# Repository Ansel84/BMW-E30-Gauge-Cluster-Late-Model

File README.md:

# BMW E30 Gauge Cluster Late Model
The goal for this project is to reverse engineer every PCB in the gauge cluster for Late model year BMW E30's. This includes the main PCB referred to as the "Nexus" board, the SI (Service Interval) board, and the smaller boards that are part of the tachometer and speedometer gauge assemblies.

# Early Model Clusters:
If you have an early model cluster and need parts for that, check out the progress of the early model project here: https://github.com/Ansel84/BMW-E30-Gauge-Cluster-Early-Model

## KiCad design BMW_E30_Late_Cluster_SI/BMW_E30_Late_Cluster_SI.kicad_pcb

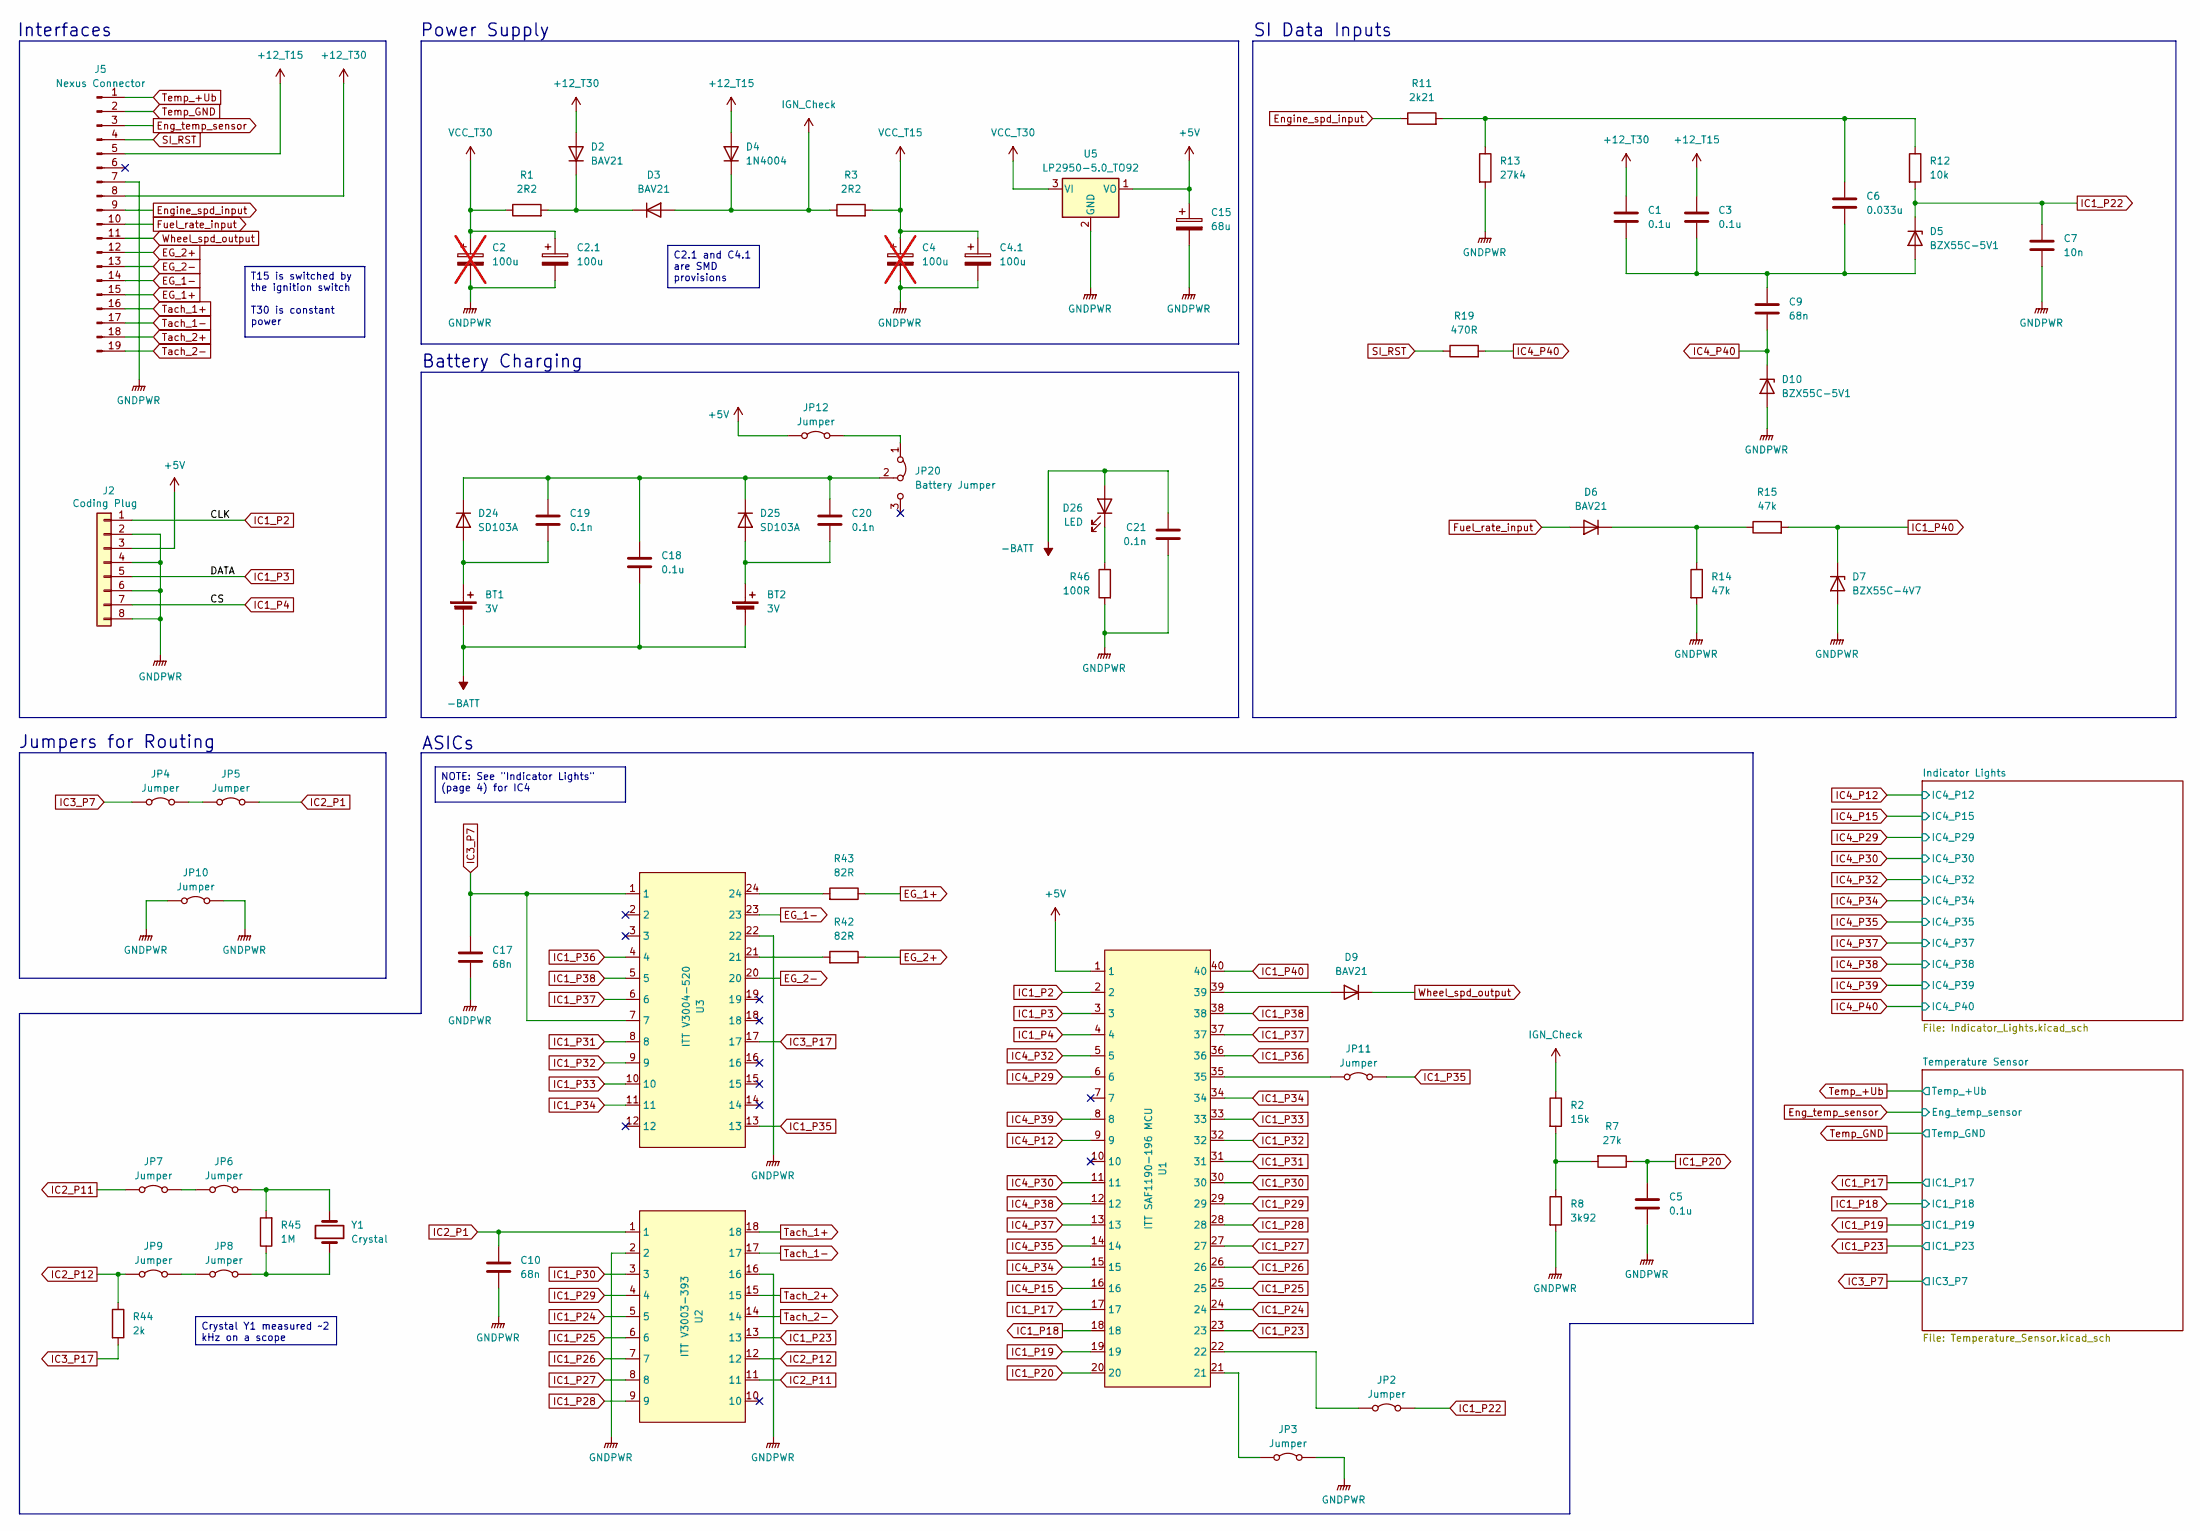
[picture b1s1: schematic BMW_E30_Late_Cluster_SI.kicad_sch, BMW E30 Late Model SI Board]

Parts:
BT1, BT2: 3V; Batt_CR14250SE
C1, C3: 0.1u; C_Disc_D6.0mm_W2.5mm_P5.00mm
C2, C4: 100u; CP_Axial_L18.0mm_D6.5mm_P25.00mm_Horizontal; not fitted
C2.1, C4.1: 100u; CP_Elec_6.3x5.8
C5, C18: 0.1u; C_Rect_L7.0mm_W2.0mm_P5.00mm
C6: 0.033u; C_Rect_L7.0mm_W2.0mm_P5.00mm
C7: 10n; C_Rect_L7.0mm_W2.0mm_P5.00mm
C9, C10, C17: 68n; C_Disc_D6.0mm_W2.5mm_P5.00mm
C15: 68u; CP_Radial_Tantal_D5.5mm_P5.00mm
C19, C20, C21: 0.1n; C_Disc_D6.0mm_W2.5mm_P5.00mm
D2, D3, D6, D9: BAV21; D_Axial_Narrow_L6.7mm_D2.4mm_P9.7mm
D4: 1N4004; D_Axial_Narrow_L6.7mm_D2.4mm_P9.7mm
D5, D10: BZX55C-5V1; D_Axial_Narrow_L6.7mm_D2.4mm_P9.7mm
D7: BZX55C-4V7; D_Axial_Narrow_L6.7mm_D2.4mm_P9.7mm
D24, D25: SD103A; D_Axial_Narrow_L6.7mm_D2.4mm_P9.7mm
D26: LED; LED_D3.0mm
J2: Coding Plug; PinSocket_1x08_P2.54mm_Horizontal
J5: Nexus Connector; E30_Early_SI_Conn_Late_P3.5
JP2, JP3, JP4, JP5, JP6, JP7, JP8, JP9, JP10, JP11, JP12: Jumper; Jumper_THT_P9.7mm
JP20: Battery Jumper; PinHeader_1x03_P2.54mm_Vertical
R1, R3: 2R2; R_Axial_Narrow_L6.8mm_D2.4mm_P9.7mm
R2: 15k; R_Axial_Narrow_L6.8mm_D2.4mm_P9.7mm
R7: 27k; R_Axial_Narrow_L6.8mm_D2.4mm_P9.7mm
R8: 3k92; R_Axial_Narrow_L6.8mm_D2.4mm_P9.7mm
R11: 2k21; R_Axial_Narrow_L6.8mm_D2.4mm_P9.7mm
R12: 10k; R_Axial_Narrow_L6.8mm_D2.4mm_P9.7mm
R13: 27k4; R_Axial_Narrow_L6.8mm_D2.4mm_P9.7mm
R14, R15: 47k; R_Axial_Narrow_L6.8mm_D2.4mm_P9.7mm
R19: 470R; R_Axial_Narrow_L6.8mm_D2.4mm_P9.7mm
R42, R43: 82R; R_Axial_Narrow_L6.8mm_D2.4mm_P9.7mm
R44: 2k; R_Axial_Narrow_L6.8mm_D2.4mm_P22.4mm
R45: 1M; R_Axial_Narrow_L6.8mm_D2.4mm_P9.7mm
R46: 100R; R_Axial_Narrow_L6.8mm_D2.4mm_P9.7mm
U1: ITT SAF1190-196 MCU; DIP-40_W15.24mm_LongPads
U2: ITT V3003-393; DIP-18_W7.62mm_LongPads
U3: ITT V3004-520; DIP-24_W15.24mm_LongPads
U5: LP2950-5.0_TO92; TO-92_Inline_Wide
Y1: Crystal; Crystal_HC18-U_Vertical

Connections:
+5V: C15.1, J2.3, JP12.1 (A), U1.1, U5.1 (VO); also elsewhere on the board
+12_T15: C3.1, D4.2 (A), J5.5
+12_T30: C1.1, D2.2 (A), J5.8; also elsewhere on the board
-BATT: BT1.2 (-), BT2.2 (-), C18.2, C21.1, D26.2 (A); also elsewhere on the board
EG_1+: J5.15, R43.1
EG_1-: J5.14, U3.23
EG_2+: J5.12, R42.1
EG_2-: J5.13, U3.20
Eng_temp_sensor: J5.3; also elsewhere on the board
Engine_spd_input: J5.9, R11.1
Fuel_rate_input: D6.2 (A), J5.10
GNDPWR: C2.2, C2.1.2, C4.2, C4.1.2, C5.2, C7.2, C10.2, C15.2, C17.2, C21.2, D7.2 (A), D10.2 (A), J2.2, J2.4, J2.6, J2.8, J5.7, JP3.1 (A), JP10.1 (A), JP10.2 (B), R8.2, R13.2, R14.2, R46.2, U2.2, U2.16, U3.22, U5.2 (GND); also elsewhere on the board
IC1_P2: J2.1, U1.2
IC1_P3: J2.5, U1.3
IC1_P4: J2.7, U1.4
IC1_P17: U1.17; also elsewhere on the board
IC1_P18: U1.18; also elsewhere on the board
IC1_P19: U1.19; also elsewhere on the board
IC1_P20: C5.1, R7.1, U1.20
IC1_P22: C7.1, D5.1 (K), JP2.1 (A), R12.2
IC1_P23: U1.23, U2.13; also elsewhere on the board
IC1_P24: U1.24, U2.5
IC1_P25: U1.25, U2.6
IC1_P26: U1.26, U2.7
IC1_P27: U1.27, U2.8
IC1_P28: U1.28, U2.9
IC1_P29: U1.29, U2.4
IC1_P30: U1.30, U2.3
IC1_P31: U1.31, U3.8
IC1_P32: U1.32, U3.9
IC1_P33: U1.33, U3.10
IC1_P34: U1.34, U3.11
IC1_P35: JP11.1 (A), U3.13
IC1_P36: U1.36, U3.4
IC1_P37: U1.37, U3.6
IC1_P38: U1.38, U3.5
IC1_P40: D7.1 (K), R15.2, U1.40
IC2_P1: C10.1, JP5.2 (B), U2.1
IC2_P11: JP7.2 (B), U2.11
IC2_P12: JP9.1 (A), R44.1, U2.12
IC3_P7: C17.1, JP4.1 (A), U3.1, U3.7; also elsewhere on the board
IC3_P17: R44.2, U3.17
IC4_P12: U1.9; also elsewhere on the board
IC4_P15: U1.16; also elsewhere on the board
IC4_P29: U1.6; also elsewhere on the board
IC4_P30: U1.11; also elsewhere on the board
IC4_P32: U1.5; also elsewhere on the board
IC4_P34: U1.15; also elsewhere on the board
IC4_P35: U1.14; also elsewhere on the board
IC4_P37: U1.13; also elsewhere on the board
IC4_P38: U1.12; also elsewhere on the board
IC4_P39: U1.8; also elsewhere on the board
IC4_P40: C9.2, D10.1 (K), R19.2; also elsewhere on the board
IGN_Check: D3.2 (A), D4.1 (K), R2.1, R3.1
unnamed: BT1.1 (+), C19.2, D24.2 (A)
unnamed: BT2.1 (+), C20.2, D25.2 (A)
unnamed: C6.1, R11.2, R12.1, R13.1
unnamed: D2.1 (K), D3.1 (K), R1.2
unnamed: C1.2, C3.2, C6.2, C9.1, D5.2 (A)
unnamed: D6.1 (K), R14.1, R15.1
unnamed: D9.2 (A), U1.39
unnamed: C18.1, C19.1, C20.1, D24.1 (K), D25.1 (K), JP20.2 (C)
unnamed: D26.1 (K), R46.1
unnamed: JP2.2 (B), U1.22
unnamed: JP3.2 (B), U1.21
unnamed: JP4.2 (B), JP5.1 (A)
unnamed: JP6.1 (A), JP7.1 (A)
unnamed: JP6.2 (B), R45.2, Y1.2
unnamed: JP8.1 (A), JP9.2 (B)
unnamed: JP8.2 (B), R45.1, Y1.1
unnamed: JP11.2 (B), U1.35
unnamed: JP12.2 (B), JP20.1 (A)
unnamed: R2.2, R7.2, R8.1
unnamed: R42.2, U3.21
unnamed: R43.2, U3.24
SI_RST: J5.4, R19.1
Tach_1+: J5.16, U2.18
Tach_1-: J5.17, U2.17
Tach_2+: J5.18, U2.15
Tach_2-: J5.19, U2.14
Temp_+Ub: J5.1; also elsewhere on the board
Temp_GND: J5.2; also elsewhere on the board
VCC_T15: C4.1, C4.1.1, R3.2; also elsewhere on the board
VCC_T30: C2.1, C2.1.1, R1.1, U5.3 (VI)
Wheel_spd_output: D9.1 (K), J5.11

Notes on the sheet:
Power Supply
Jumpers for Routing
Battery Charging
Interfaces
ASICs
SI Data Inputs
C2.1 and C4.1 are SMD provisions
T15 is switched by the ignition switch T30 is constant power
NOTE: See "Indicator Lights" (page 4) for IC4
Crystal Y1 measured ~2 kHz on a scope

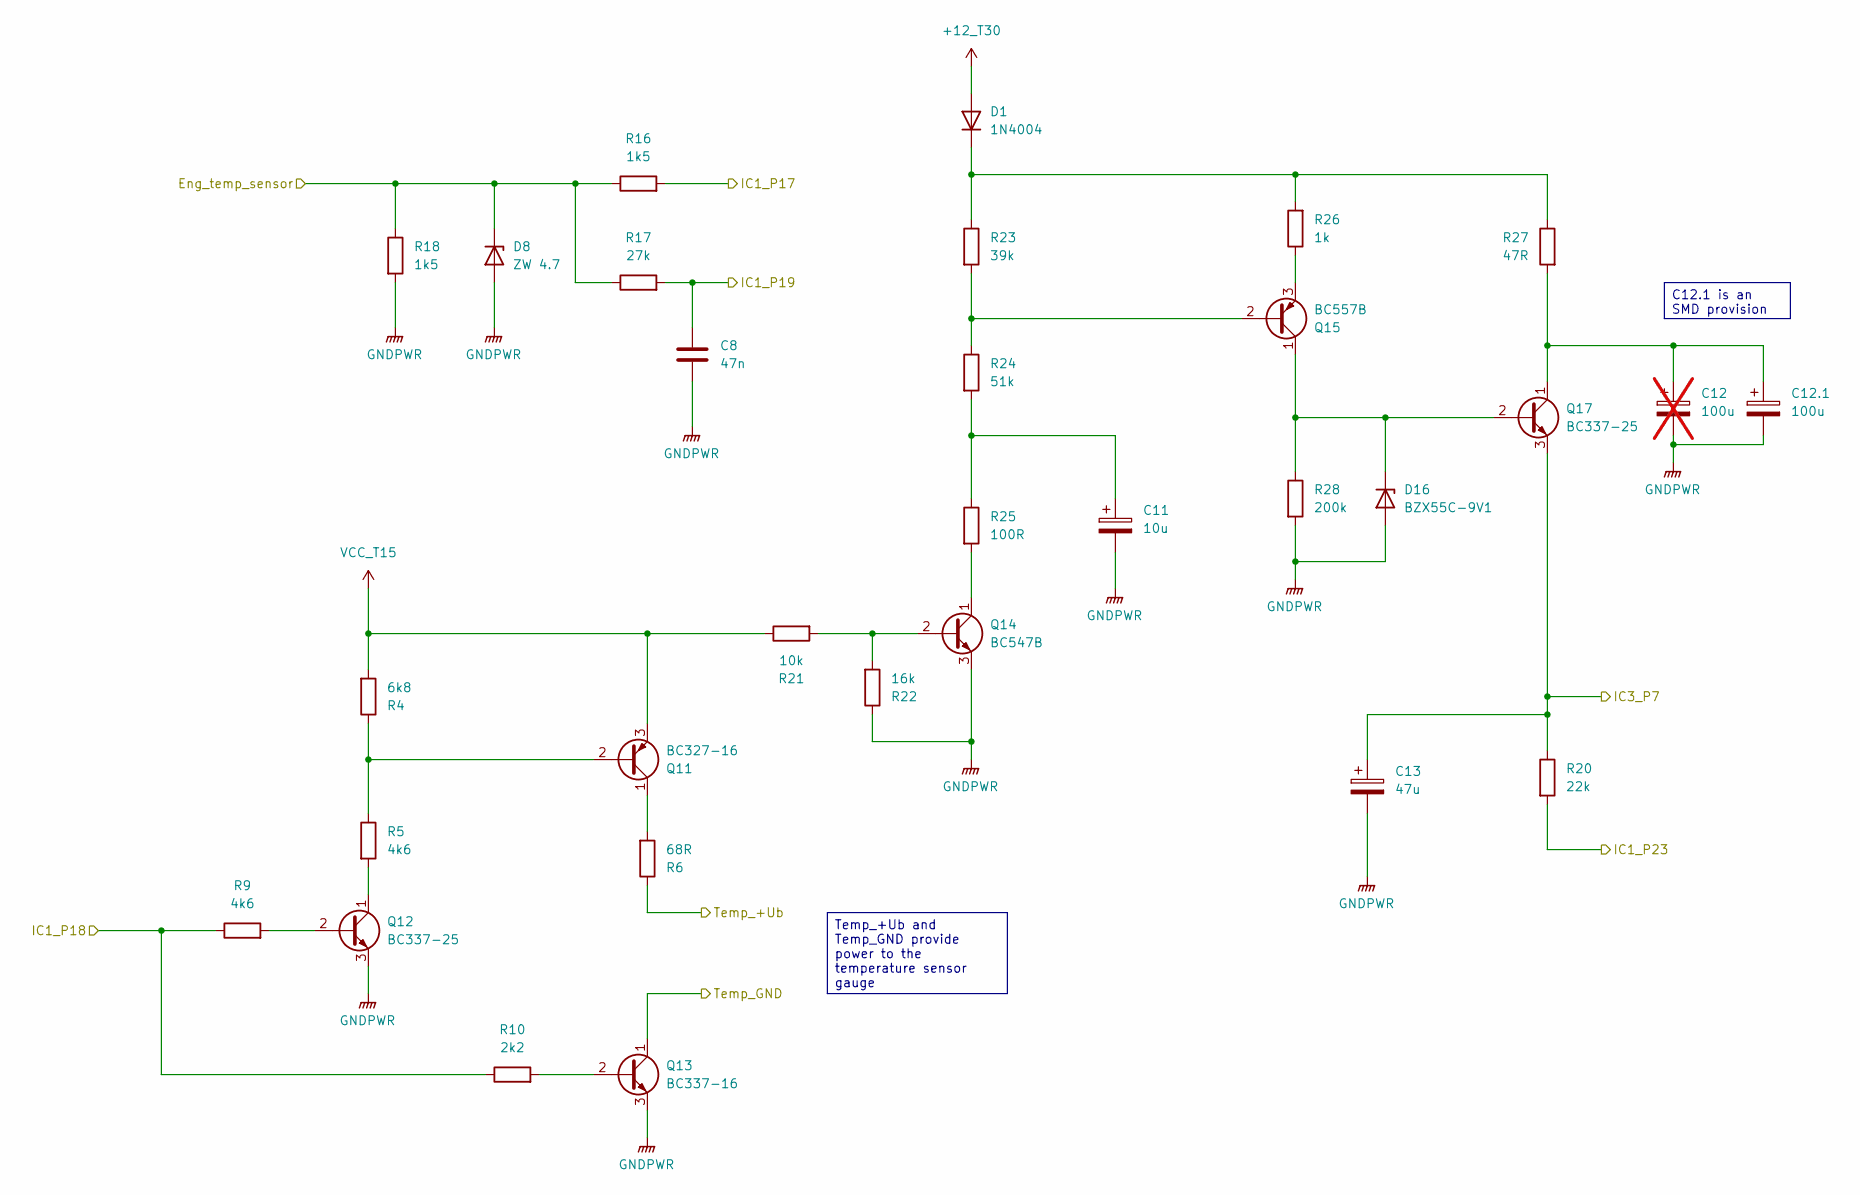
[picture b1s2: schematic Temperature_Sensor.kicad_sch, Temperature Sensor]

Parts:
C8: 47n; C_Disc_D6.0mm_W2.5mm_P5.00mm
C11: 10u; CP_Radial_Tantal_D8.0mm_P2.50mm
C12: 100u; CP_Axial_L18.0mm_D6.5mm_P25.00mm_Horizontal; not fitted
C12.1: 100u; CP_Elec_6.3x5.8
C13: 47u; CP_Radial_Tantal_D9.0mm_P2.50mm
D1: 1N4004; D_Axial_Narrow_L6.7mm_D2.4mm_P9.7mm
D8: ZW 4.7; D_Axial_Narrow_L6.7mm_D2.4mm_P9.7mm
D16: BZX55C-9V1; D_Axial_Narrow_L6.7mm_D2.4mm_P9.7mm
Q11: BC327-16; TO-92_Inline_Wide
Q12, Q17: BC337-25; TO-92_Inline_Wide
Q13: BC337-16; TO-92_Inline_Wide
Q14: BC547B; TO-92_Inline_Wide
Q15: BC557B; TO-92_Inline_Wide
R4: 6k8; R_Axial_Narrow_L6.8mm_D2.4mm_P9.7mm
R5, R9: 4k6; R_Axial_Narrow_L6.8mm_D2.4mm_P9.7mm
R6: 68R; R_Axial_DIN0414_L11.9mm_D4.5mm_P20.32mm_Horizontal
R10: 2k2; R_Axial_Narrow_L6.8mm_D2.4mm_P9.7mm
R16, R18: 1k5; R_Axial_Narrow_L6.8mm_D2.4mm_P9.7mm
R17: 27k; R_Axial_Narrow_L6.8mm_D2.4mm_P9.7mm
R20: 22k; R_Axial_DIN0207_L6.3mm_D2.5mm_P22.2mm_Horizontal
R21: 10k; R_Axial_Narrow_L6.8mm_D2.4mm_P9.7mm
R22: 16k; R_Axial_Narrow_L6.8mm_D2.4mm_P9.7mm
R23: 39k; R_Axial_Narrow_L6.8mm_D2.4mm_P9.7mm
R24: 51k; R_Axial_Narrow_L6.8mm_D2.4mm_P9.7mm
R25: 100R; R_Axial_Narrow_L6.8mm_D2.4mm_P9.7mm
R26: 1k; R_Axial_Narrow_L6.8mm_D2.4mm_P9.7mm
R27: 47R; R_Axial_DIN0516_L15.5mm_D5.0mm_P20.32mm_Horizontal
R28: 200k; R_Axial_Narrow_L6.8mm_D2.4mm_P9.7mm

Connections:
+12_T30: D1.2 (A); also elsewhere on the board
Eng_temp_sensor: D8.1 (K), R16.1, R17.1, R18.1; also elsewhere on the board
GNDPWR: C8.2, C11.2, C12.2, C12.1.2, C13.2, D8.2 (A), D16.2 (A), Q12.3 (E), Q13.3 (E), Q14.3 (E), R18.2, R22.1, R28.2; also elsewhere on the board
IC1_P17: R16.2; also elsewhere on the board
IC1_P18: R9.1, R10.1; also elsewhere on the board
IC1_P19: C8.1, R17.2; also elsewhere on the board
IC1_P23: R20.2; also elsewhere on the board
IC3_P7: C13.1, Q17.3 (E), R20.1; also elsewhere on the board
unnamed: C11.1, R24.2, R25.1
unnamed: D1.1 (K), R23.1, R26.2, R27.1
unnamed: D16.1 (K), Q15.1 (C), Q17.2 (B), R28.1
unnamed: Q11.2 (B), R4.1, R5.1
unnamed: Q11.1 (C), R6.2
unnamed: Q12.2 (B), R9.2
unnamed: Q12.1 (C), R5.2
unnamed: Q13.2 (B), R10.2
unnamed: Q14.2 (B), R21.2, R22.2
unnamed: Q14.1 (C), R25.2
unnamed: Q15.2 (B), R23.2, R24.1
unnamed: Q15.3 (E), R26.1
unnamed: C12.1, C12.1.1, Q17.1 (C), R27.2
Temp_+Ub: R6.1; also elsewhere on the board
Temp_GND: Q13.1 (C); also elsewhere on the board
VCC_T15: Q11.3 (E), R4.2, R21.1; also elsewhere on the board

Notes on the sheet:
Temp_+Ub and Temp_GND provide power to the temperature sensor gauge
C12.1 is an SMD provision

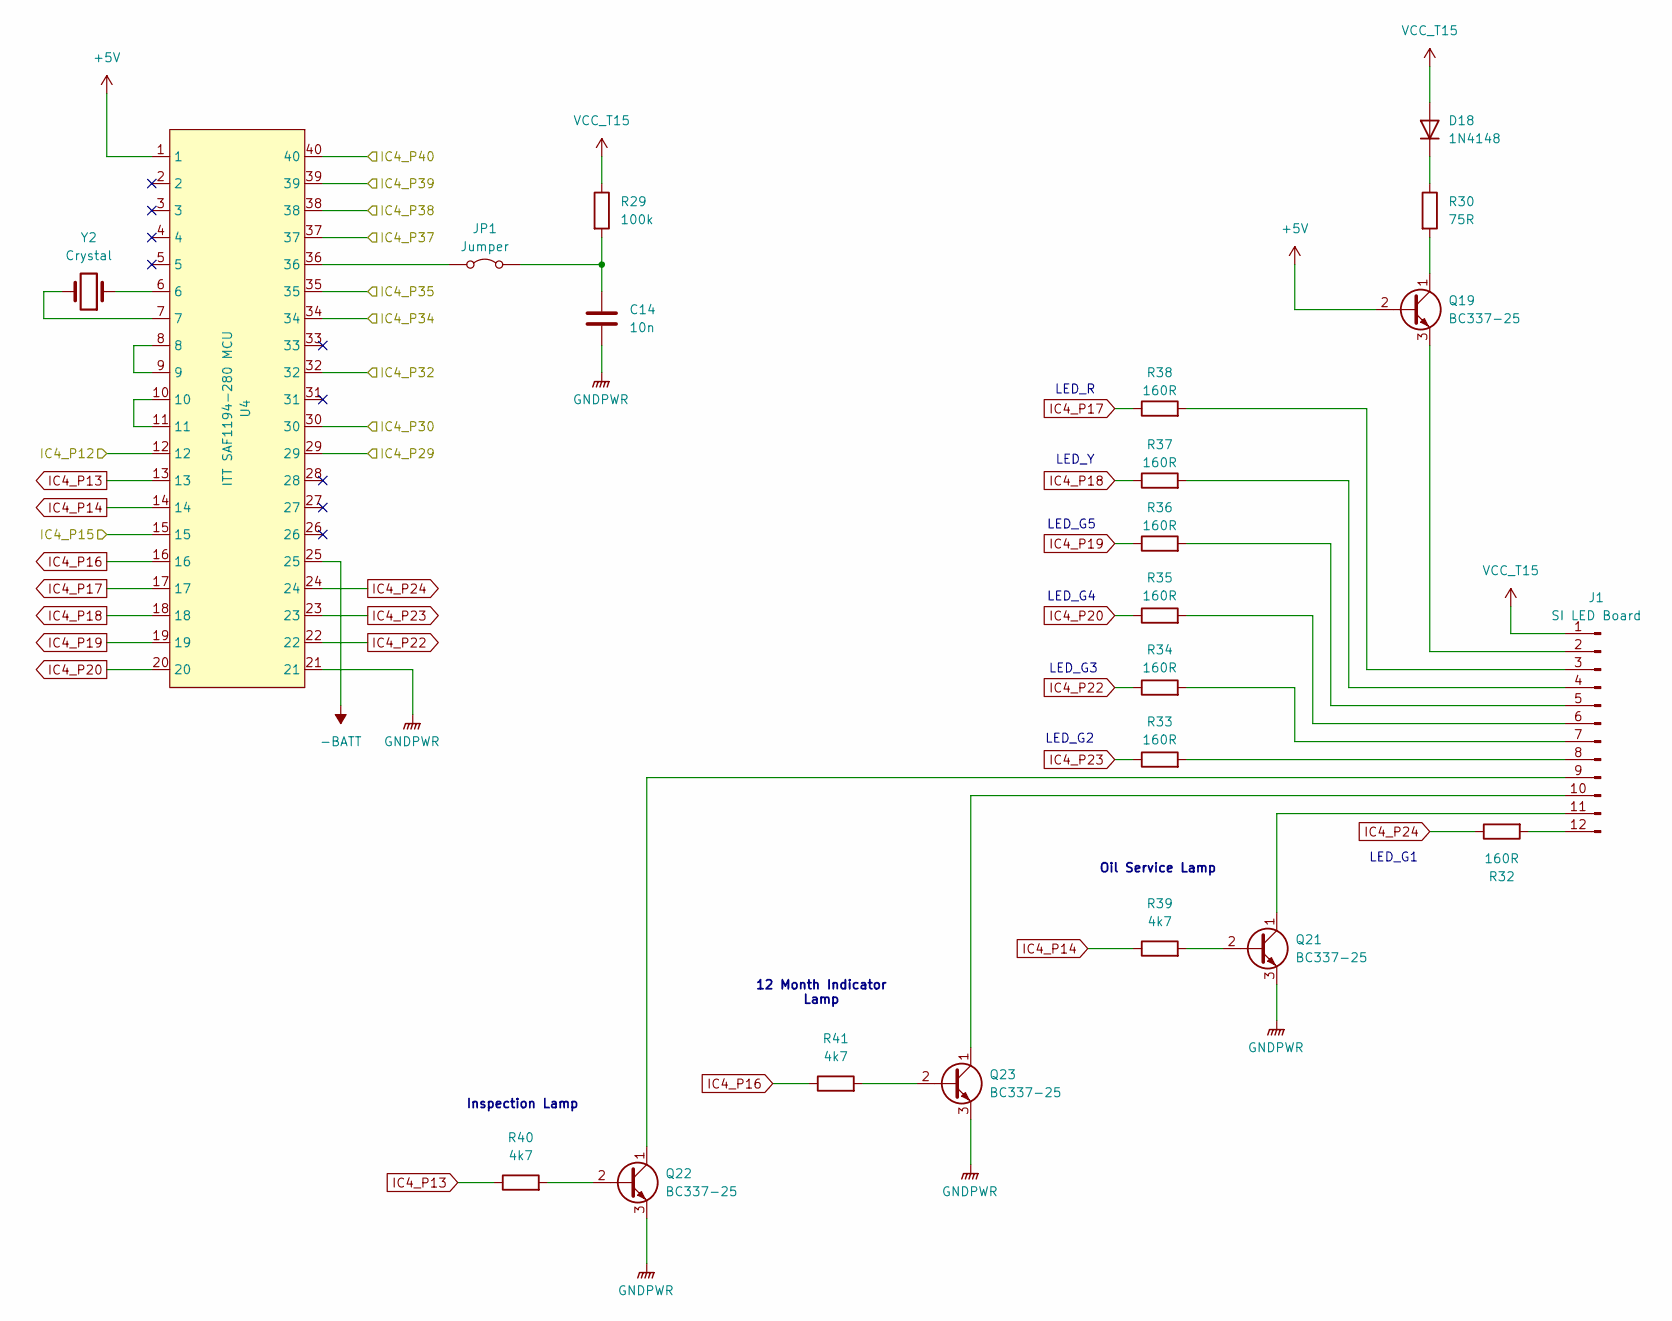
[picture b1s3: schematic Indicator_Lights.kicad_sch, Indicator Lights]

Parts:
C14: 10n; C_Disc_D6.0mm_W2.5mm_P5.00mm
D18: 1N4148; D_Axial_Narrow_L6.7mm_D2.4mm_P9.7mm
J1: SI LED Board; SILight_1x12_P2.54mm_Vertical_PinHeader
JP1: Jumper; Jumper_THT_P9.7mm
Q19, Q21, Q22, Q23: BC337-25; TO-92_Inline_Wide
R29: 100k; R_Axial_Narrow_L6.8mm_D2.4mm_P9.7mm
R30: 75R; R_Axial_Narrow_L6.8mm_D2.4mm_P9.7mm
R32, R33, R34, R35, R36, R37, R38: 160R; R_Axial_Narrow_L6.8mm_D2.4mm_P9.7mm
R39, R40, R41: 4k7; R_Axial_Narrow_L6.8mm_D2.4mm_P9.7mm
U4: ITT SAF1194-280 MCU; DIP-40_W15.24mm_LongPads
Y2: Crystal; Crystal_C38-LF_D3.0mm_L8.0mm_Horizontal

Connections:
+5V: Q19.2 (B), U4.1; also elsewhere on the board
-BATT: U4.25; also elsewhere on the board
GNDPWR: C14.2, Q21.3 (E), Q22.3 (E), Q23.3 (E), U4.21; also elsewhere on the board
IC4_P12: U4.12; also elsewhere on the board
IC4_P13: R40.1, U4.13
IC4_P14: R39.1, U4.14
IC4_P15: U4.15; also elsewhere on the board
IC4_P16: R41.1, U4.16
IC4_P17: R38.1, U4.17
IC4_P18: R37.1, U4.18
IC4_P19: R36.1, U4.19
IC4_P20: R35.1, U4.20
IC4_P22: R34.1, U4.22
IC4_P23: R33.1, U4.23
IC4_P24: R32.1, U4.24
IC4_P29: U4.29; also elsewhere on the board
IC4_P30: U4.30; also elsewhere on the board
IC4_P32: U4.32; also elsewhere on the board
IC4_P34: U4.34; also elsewhere on the board
IC4_P35: U4.35; also elsewhere on the board
IC4_P37: U4.37; also elsewhere on the board
IC4_P38: U4.38; also elsewhere on the board
IC4_P39: U4.39; also elsewhere on the board
IC4_P40: U4.40; also elsewhere on the board
unnamed: D18.1 (K), R30.1
unnamed: J1.2, Q19.3 (E)
unnamed: J1.3, R38.2
unnamed: J1.4, R37.2
unnamed: J1.5, R36.2
unnamed: J1.6, R35.2
unnamed: J1.7, R34.2
unnamed: J1.8, R33.2
unnamed: J1.9, Q22.1 (C)
unnamed: J1.10, Q23.1 (C)
unnamed: J1.11, Q21.1 (C)
unnamed: J1.12, R32.2
unnamed: JP1.1 (A), U4.36
unnamed: C14.1, JP1.2 (B), R29.2
unnamed: Q19.1 (C), R30.2
unnamed: Q21.2 (B), R39.2
unnamed: Q22.2 (B), R40.2
unnamed: Q23.2 (B), R41.2
unnamed: U4.6, Y2.1
unnamed: U4.7, Y2.2
unnamed: U4.8, U4.9
unnamed: U4.10, U4.11
VCC_T15: D18.2 (A), J1.1, R29.1; also elsewhere on the board

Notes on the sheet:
Oil Service Lamp
LED_G1
LED_G3
LED_G5
LED_R
Inspection Lamp
LED_G2
LED_Y
12 Month Indicator Lamp
LED_G4

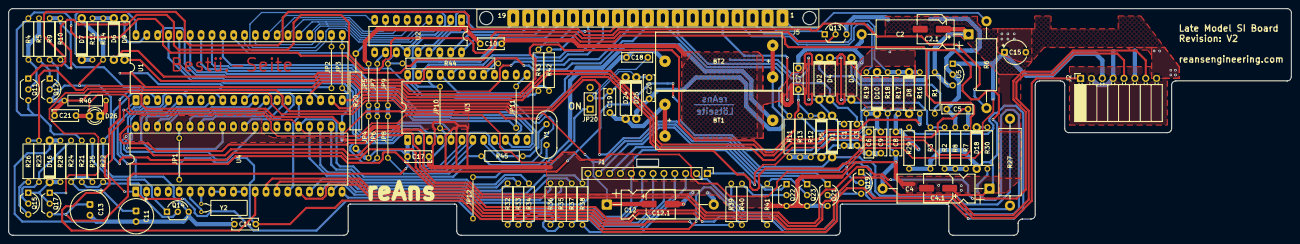
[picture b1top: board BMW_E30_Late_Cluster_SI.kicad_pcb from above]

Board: 2 copper layers, 300.0 x 53.0 mm, 118 parts (0 on the bottom side), 130 nets.

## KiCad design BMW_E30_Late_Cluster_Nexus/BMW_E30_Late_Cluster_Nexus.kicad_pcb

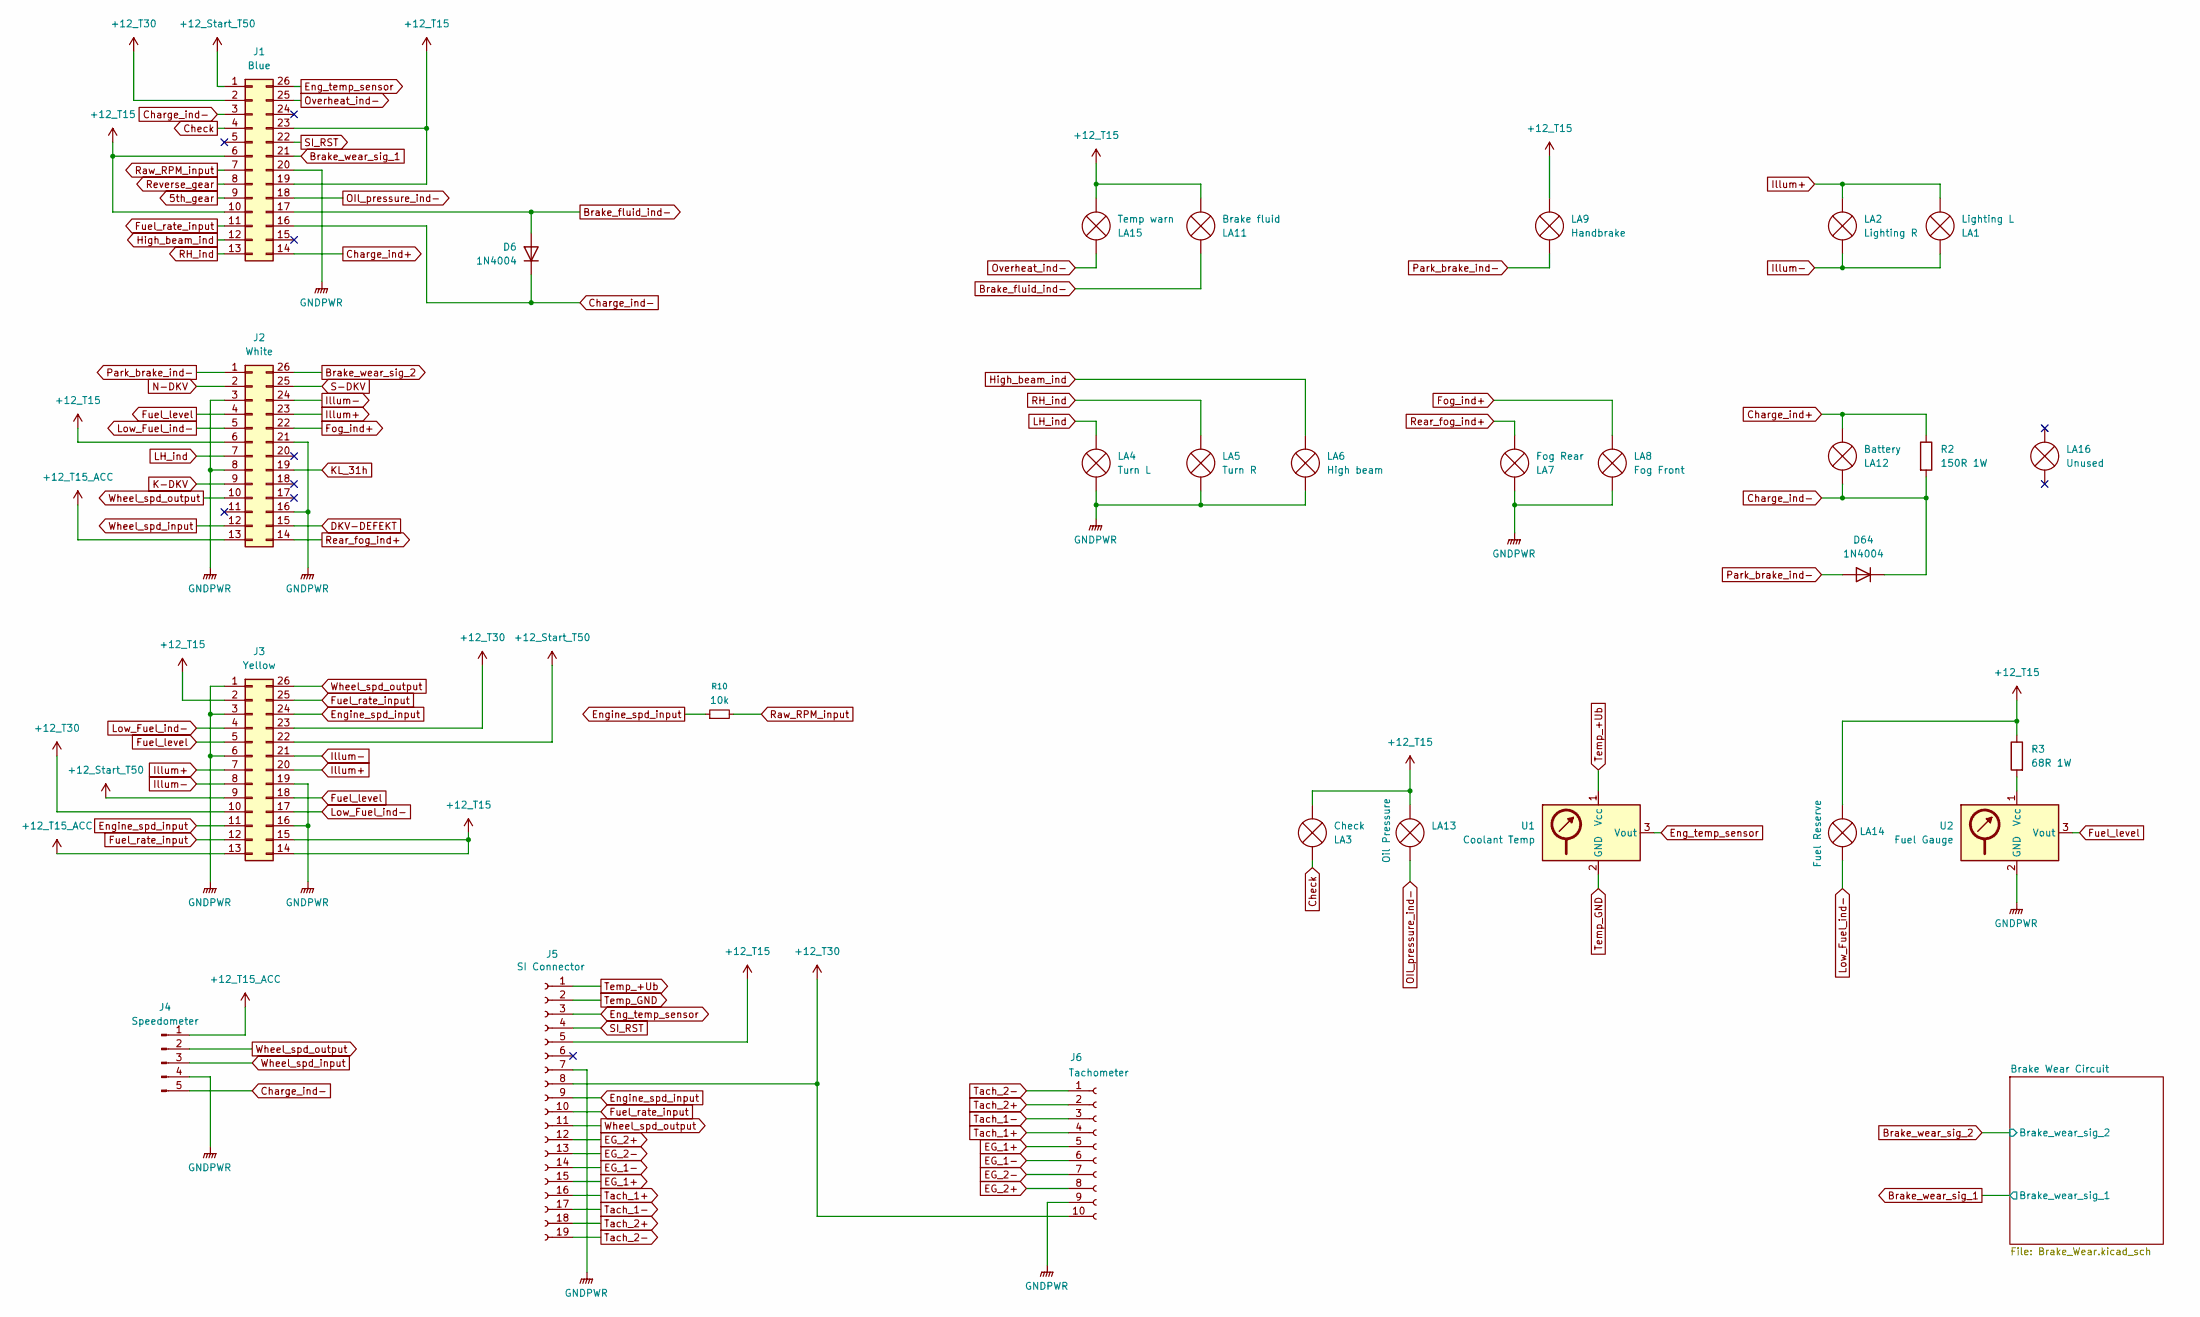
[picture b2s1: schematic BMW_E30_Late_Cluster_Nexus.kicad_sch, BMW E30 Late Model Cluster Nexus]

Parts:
D6: 1N4004; D_DO-41_SOD81_P12.70mm_Horizontal
D64: 1N4004; D_DO-41_SOD81_P10.16mm_Horizontal
J1: Blue; TE_827881-3
J2: White; TE_827881-2
J3: Yellow; TE_827881-1
J4: Speedometer; ConnectorIV_Late
J5: SI Connector; ConnectorV_Late_V2
J6: Tachometer; Tach_EG_Socket_Late
LA1: Lighting L; 2821MF
LA2: Lighting R; 2821MF
LA3: Check; 2721MF
LA4: Turn L; 2721MF
LA5: Turn R; 2721MF
LA6: High beam; 2721MF
LA7: Fog Rear; 2721MF
LA8: Fog Front; 2721MF
LA9: Handbrake; 2721MF
LA11: Brake fluid; 2721MF
LA12: Battery; 2721MF
LA13: Oil Pressure; 2721MF
LA14: Fuel Reserve; 2721MF
LA15: Temp warn; 2721MF
LA16: Unused; 2721MF
R2: 150R 1W; R_Axial_DIN0414_L11.9mm_D4.5mm_P20.32mm_Horizontal; Digikey Part # A131434CT-ND
R3: 68R 1W; R_Axial_DIN0414_L11.9mm_D4.5mm_P20.32mm_Horizontal
R10: 10k; R_Axial_DIN0207_L6.3mm_D2.5mm_P10.16mm_Horizontal
U1: Coolant Temp; Gauge_Temp
U2: Fuel Gauge; Gauge_Fuel

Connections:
5th_gear: J1.9
+12_Start_T50: J1.1, J3.9, J3.22; also elsewhere on the board
+12_T15: J1.6, J1.10, J1.19, J1.23, J2.6, J3.2, J3.14, J3.15, J5.5, LA3.1 (-), LA9.1 (-), LA11.2 (+), LA13.2 (+), LA14.1 (-), LA15.1 (-), R3.1; also elsewhere on the board
+12_T15_ACC: J2.13, J3.13, J4.1
+12_T30: J1.2, J3.10, J3.23, J5.8, J6.10
Brake_fluid_ind-: D6.2 (A), J1.17, LA11.1 (-)
Brake_wear_sig_1: J1.21; also elsewhere on the board
Brake_wear_sig_2: J2.26; also elsewhere on the board
Charge_ind+: J1.14, LA12.1 (-), R2.1
Charge_ind-: D6.1 (K), D64.1 (K), J1.3, J1.16, J4.5, LA12.2 (+), R2.2
Check: J1.4, LA3.2 (+)
DKV-DEFEKT: J2.15
EG_1+: J5.15, J6.5
EG_1-: J5.14, J6.6
EG_2+: J5.12, J6.8
EG_2-: J5.13, J6.7
Eng_temp_sensor: J1.26, J5.3, U1.3 (Vout)
Engine_spd_input: J3.11, J3.24, J5.9, R10.1
Fog_ind+: J2.22, LA8.1 (-)
Fuel_level: J2.4, J3.5, J3.18, U2.3 (Vout)
Fuel_rate_input: J1.11, J3.12, J3.25, J5.10
GNDPWR: J1.20, J2.3, J2.8, J2.16, J2.21, J3.1, J3.3, J3.6, J3.16, J3.19, J4.4, J5.7, J6.9, LA4.2 (+), LA5.2 (+), LA6.1 (-), LA7.1 (-), LA8.2 (+), U2.2 (GND); also elsewhere on the board
High_beam_ind: J1.12, LA6.2 (+)
Illum+: J2.23, J3.7, J3.20, LA1.2 (+), LA2.1 (-)
Illum-: J2.24, J3.8, J3.21, LA1.1 (-), LA2.2 (+)
K-DKV: J2.9
KL_31h: J2.19
LH_ind: J2.7, LA4.1 (-)
Low_Fuel_ind-: J2.5, J3.4, J3.17, LA14.2 (+)
N-DKV: J2.2
unnamed: R3.2, U2.1 (Vcc)
OIl_pressure_ind-: J1.18, LA13.1 (-)
Overheat_ind-: J1.25, LA15.2 (+)
Park_brake_ind-: D64.2 (A), J2.1, LA9.2 (+)
RH_ind: J1.13, LA5.1 (-)
Raw_RPM_input: J1.7, R10.2
Rear_fog_ind+: J2.14, LA7.2 (+)
Reverse_gear: J1.8
S-DKV: J2.25
SI_RST: J1.22, J5.4
Tach_1+: J5.16, J6.4
Tach_1-: J5.17, J6.3
Tach_2+: J5.18, J6.2
Tach_2-: J5.19, J6.1
Temp_+Ub: J5.1, U1.1 (Vcc)
Temp_GND: J5.2, U1.2 (GND)
Wheel_spd_input: J2.12, J4.3
Wheel_spd_output: J2.10, J3.26, J4.2, J5.11

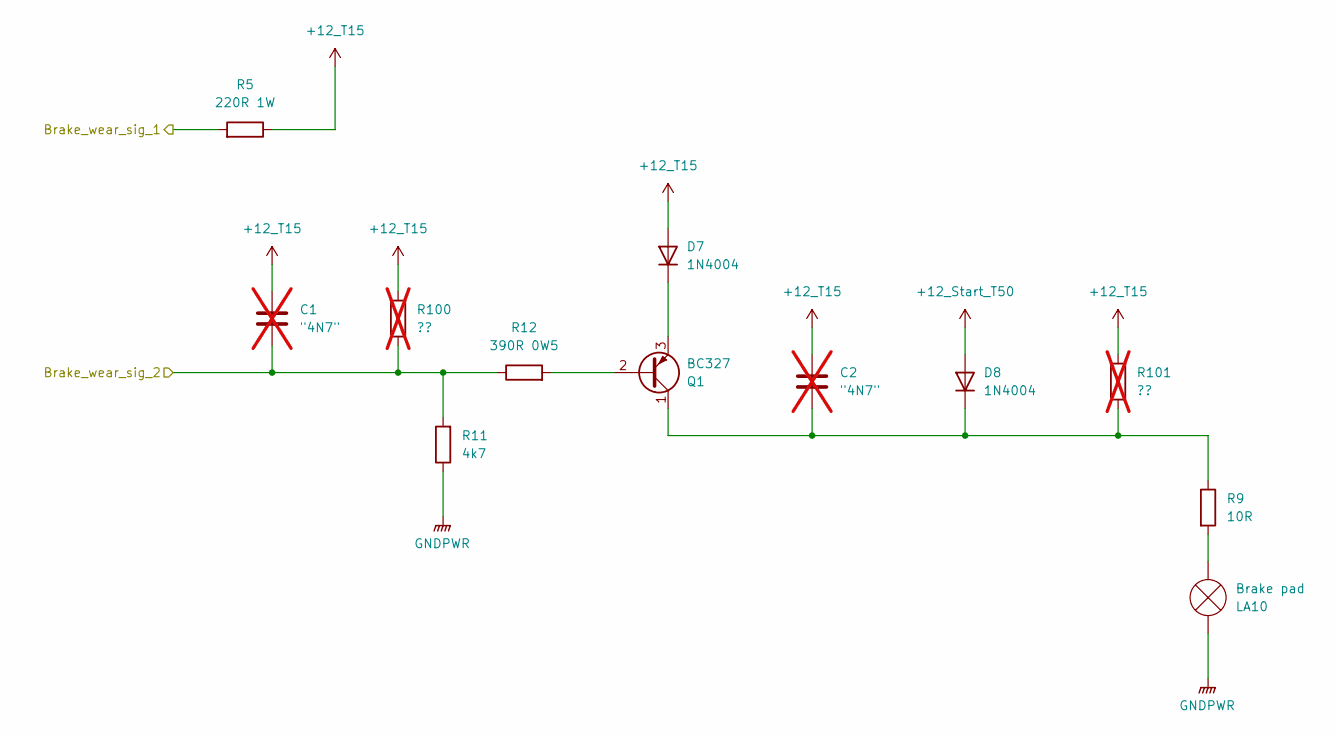
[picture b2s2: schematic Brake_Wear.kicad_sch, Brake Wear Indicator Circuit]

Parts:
C1, C2: "4N7"; not fitted
D7, D8: 1N4004; D_DO-41_SOD81_P12.70mm_Horizontal
LA10: Brake pad; 2721MF
Q1: BC327; TO-92_Inline_Wide
R5: 220R 1W; R_Axial_DIN0414_L11.9mm_D4.5mm_P20.32mm_Horizontal
R9: 10R; R_Axial_DIN0207_L6.3mm_D2.5mm_P15.24mm_Horizontal
R11: 4k7; R_Axial_DIN0207_L6.3mm_D2.5mm_P15.24mm_Horizontal
R12: 390R 0W5; R_Axial_DIN0309_L9.0mm_D3.2mm_P15.24mm_Horizontal
R100, R101: ??; R_Axial_DIN0207_L6.3mm_D2.5mm_P15.24mm_Horizontal; not fitted

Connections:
+12_Start_T50: D8.2 (A); also elsewhere on the board
+12_T15: C1.1, C2.1, D7.2 (A), R5.1, R100.2, R101.2; also elsewhere on the board
Brake_wear_sig_1: R5.2; also elsewhere on the board
Brake_wear_sig_2: C1.2, R11.2, R12.1, R100.1; also elsewhere on the board
GNDPWR: LA10.1 (-), R11.1; also elsewhere on the board
unnamed: D7.1 (K), Q1.3 (E)
unnamed: C2.2, D8.1 (K), Q1.1 (C), R9.1, R101.1
unnamed: LA10.2 (+), R9.2
unnamed: Q1.2 (B), R12.2

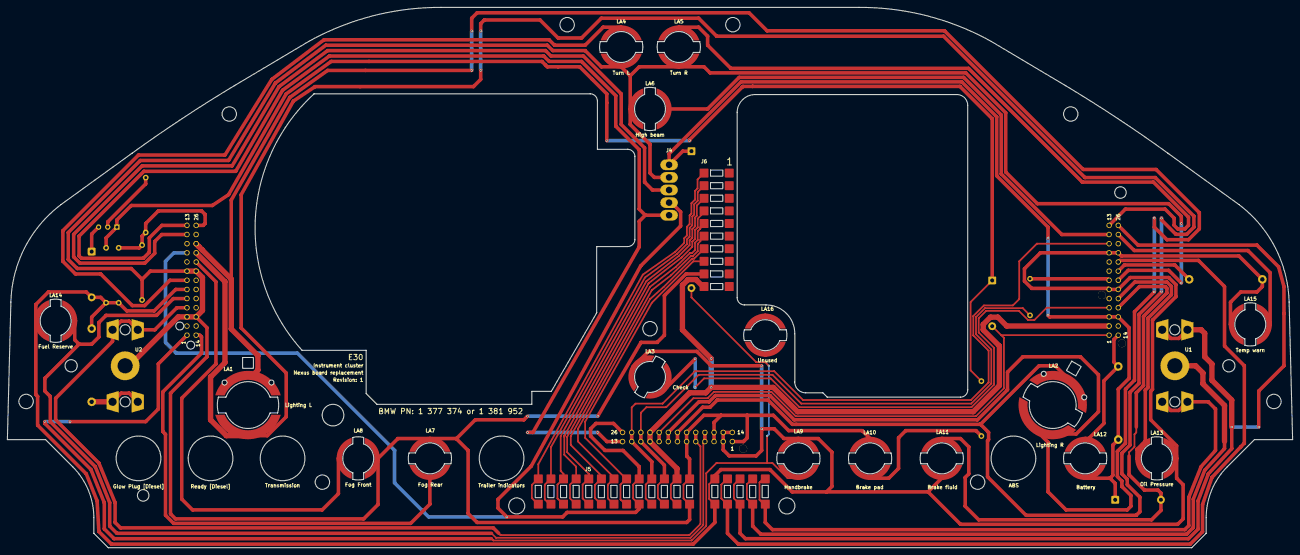
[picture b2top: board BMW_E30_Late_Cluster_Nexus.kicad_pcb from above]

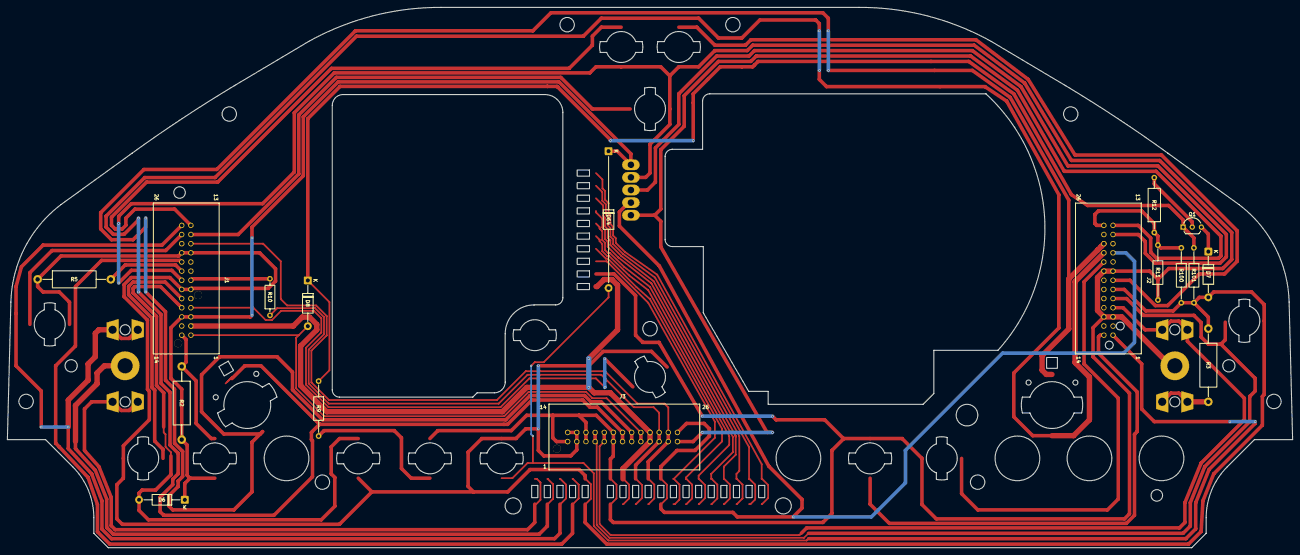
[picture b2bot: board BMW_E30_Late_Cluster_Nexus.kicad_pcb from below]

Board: 2 copper layers, 356.8 x 150.0 mm, 38 parts (17 on the bottom side), 45 nets.
